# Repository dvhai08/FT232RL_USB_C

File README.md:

# FT232RL_USB_C

FT232RL-based UART to USB Type-C adapter with support of 3V3

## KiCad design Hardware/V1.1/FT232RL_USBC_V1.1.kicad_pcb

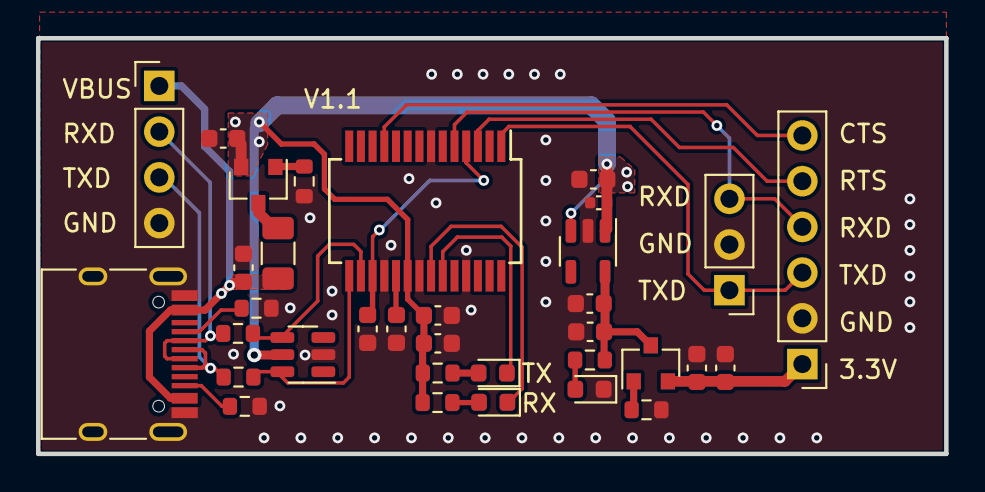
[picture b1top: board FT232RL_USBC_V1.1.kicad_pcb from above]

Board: 2 copper layers, 50.5 x 23.1 mm, 35 parts (1 on the bottom side), 25 nets.

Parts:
C1: 10nF; C_0603_1608Metric
C2, C6, C8, C19: 4.7uF; C_0603_1608Metric
C3, C4, C7, C9, C20, C31: 100nF; C_0603_1608Metric
C5: 100nF; C_0402_1005Metric
D1, D2, D3: LED; LED_0603_1608Metric
D4: SP0505BAHT; SOT-23-6
F1: 500mA; Fuse_1206_3216Metric
J1: USB_C_Receptacle_USB2.0; USB_C_Receptacle_HRO_TYPE-C-31-M-12
J2: Main Header; PinHeader_1x06_P2.54mm_Vertical
J3: USB Header; PinHeader_1x04_P2.54mm_Vertical
J4: Sub Header; PinHeader_1x03_P2.54mm_Vertical
Q1, Q2: BSS84; SOT-23
R1, R2: 5.1K; R_0603_1608Metric
R3, R4, R5, R6, R9: 1K; R_0603_1608Metric
R7, R8: 10R; R_0603_1608Metric
U1: AP2112K-3.3; SOT-23-5
U2: FT232RL; SSOP-28_5.3x10.2mm_P0.65mm
U5: IKY; LoGo12mm

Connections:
+3V3: C6.1, C7.1, Q1.3 (D), R5.1, U1.5 (VOUT)
+5V: C2.1, C5.1, C19.1, C20.1, C31.1, D4.5 (K), Q2.2 (S), R3.1, R4.1, U1.1 (VIN), U1.3 (EN), U2.20 (VCC)
/+3.3V_OUT: C8.1, C9.1, J2.1, Q1.2 (S)
/CTS: J2.6, U2.11 (CTS)
/RTS: J2.5, U2.3 (RTS)
/RXD: J2.4, J4.3, U2.5 (RXD)
/RX_LED: D2.1 (K), U2.22 (CBUS1)
/TXD: J2.3, J4.1, U2.1 (TXD)
/TX_LED: D1.1 (K), U2.23 (CBUS0)
/USB_DN: J1.A7 (D-), J1.B7 (D-), J3.2, R7.1
/USB_DP: J1.A6 (D+), J1.B6 (D+), J3.3, R8.1
GND: C1.2, C2.2, C3.2, C4.2, C5.2, C6.2, C7.2, C8.2, C9.2, C19.2, C20.2, C31.2, D3.1 (K), D4.2 (A), J1.A1 (GND), J1.A12 (GND), J1.B1 (GND), J1.B12 (GND), J1.S1 (SHIELD), J2.2, J3.4, J4.2, R1.2, R2.2, R6.2, R9.2, U1.2 (GND), U2.7 (GND), U2.18 (GND), U2.21 (GND), U2.25 (AGND)
unnamed: C3.1, U2.19 (~RESET)
unnamed: C4.1, U2.4 (VCCIO), U2.17 (3V3OUT)
unnamed: D1.2 (A), R3.2
unnamed: D2.2 (A), R4.2
unnamed: D3.2 (A), R5.2
unnamed: D4.4 (K), R7.2, U2.16 (USBD-)
unnamed: F1.2, Q2.3 (D)
unnamed: J1.A5 (CC1), R1.1
unnamed: J1.B5 (CC2), R2.1
unnamed: Q1.1 (G), R6.1
unnamed: Q2.1 (G), R9.1
unnamed: D4.6 (K), R8.2, U2.15 (USBD+)
VBUS: C1.1, F1.1, J1.A4 (VBUS), J1.A9 (VBUS), J1.B4 (VBUS), J1.B9 (VBUS), J3.1

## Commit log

2023-09-11 V1.1
